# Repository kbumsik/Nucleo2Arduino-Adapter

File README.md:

Universal Shields Adapter for STM32 Nucleo 64 boards
====================================================

Universal Adapter for Nucleo 64 boards that supports various expansion boards
including:

* STM32 Nucleo pinsas a mother
* Arduino shields, **including ICSP(SPI) pins**
* TI BoosterPack (LaunchPad) 40-pin
* 2 x Atmel Xplained Pro expansion boards

Image (v0.5 test board)
=======================

Why?
====

STM32 Nucleo boards are awesome development boards to start a microcontroller
project. However, ther is a caveat: it does not have variaous expansion boards.
Even though Nucleo boards have Arduino-compatible header pins, a problem still
aries here:

> *Nucleo boards do not have Arduino ICSP/SPI pins!*

Absence of ICSP pins losses supports for various arduino shields. So I decided
to make an adapter shield to support for Arduino shields. Making this adapter I
also added some headers for other companies expansion boards like TI's BoosterPack.

I believe this adapter will remove nasty wiring jobs when you work with expansion boards.

Tested expansion boards
=======================
Although this adapter will support most of Arduino shields and expansion boards
we are always unexpected things making it not to supports some boards. So I attach
tested expansion boards here

* ATWINC1500 Xplained Pro

Please email me (kbumsik@gmail.com) or PR if you tested other boards.

External Libraries Used
=======================
I used the following libraries:

* [KiCad Library](https://github.com/KiCad/kicad-library/tree/master/template)

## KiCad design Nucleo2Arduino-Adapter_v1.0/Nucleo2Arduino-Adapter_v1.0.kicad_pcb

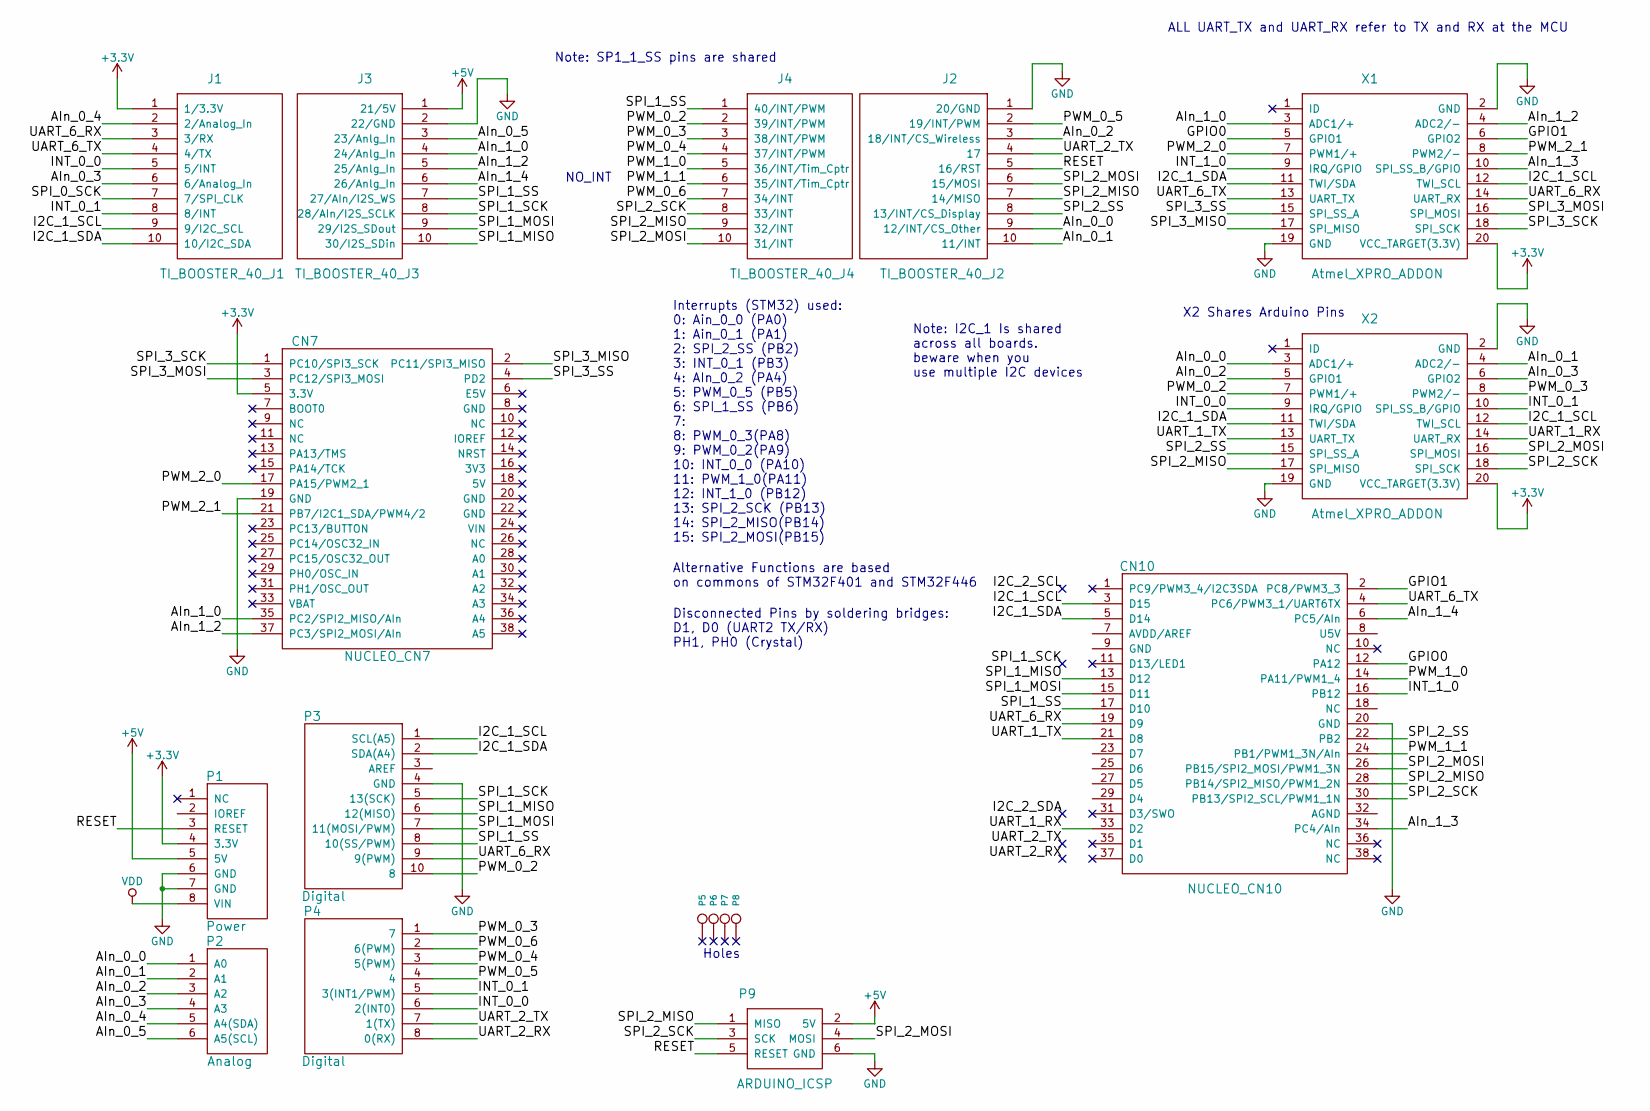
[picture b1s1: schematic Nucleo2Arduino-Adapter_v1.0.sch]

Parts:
CN7: NUCLEO_CN7; Pin_Header_Straight_2x19
CN10: NUCLEO_CN10; Pin_Header_Straight_2x19
J1: TI_BOOSTER_40_J1; SIL-10
J2: TI_BOOSTER_40_J2; SIL-10
J3: TI_BOOSTER_40_J3; SIL-10
J4: TI_BOOSTER_40_J4; SIL-10
P1: Power; Socket_Strip_Arduino_1x08
P2: Analog; Socket_Strip_Arduino_1x06
P3: Digital; Socket_Strip_Arduino_1x10
P4: Digital; Socket_Strip_Arduino_1x08
P5, P6, P7, P8: CONN_1; Arduino_1pin
P9: ARDUINO_ICSP; Pin_Header_Straight_2x03
X1, X2: Atmel_XPRO_ADDON; Pin_Header_Angled_2x10

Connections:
+3V3: CN7.5 (3.3V), J1.1 (1/3.3V), P1.4 (3.3V), X1.20 (VCC_TARGET(3.3V)), X2.20 (VCC_TARGET(3.3V))
+5V: J3.1 (21/5V), P1.5 (5V), P9.2 (5V)
/AIn_0_0: J2.9 (12/INT/CS_Other), P2.1 (A0), X2.3 (ADC1/+)
/AIn_0_1: J2.10 (11/INT), P2.2 (A1), X2.4 (ADC2/-)
/AIn_0_2: J2.3 (18/INT/CS_Wireless), P2.3 (A2), X2.5 (GPIO1)
/AIn_0_3: J1.6 (6/Analog_In), P2.4 (A3), X2.6 (GPIO2)
/AIn_0_4: J1.2 (2/Analog_In), P2.5 (A4(SDA))
/AIn_0_5: J3.3 (23/Anlg_In), P2.6 (A5(SCL))
/AIn_1_0: CN7.35 (PC2/SPI2_MISO/AIn), J3.4 (24/Anlg_In), X1.3 (ADC1/+)
/AIn_1_2: CN7.37 (PC3/SPI2_MOSI/AIn), J3.5 (25/Anlg_In), X1.4 (ADC2/-)
/AIn_1_3: CN10.34 (PC4/AIn), X1.10 (SPI_SS_B/GPIO)
/AIn_1_4: CN10.6 (PC5/AIn), J3.6 (26/Anlg_In)
/GPIO0: CN10.12 (PA12), X1.5 (GPIO1)
/GPIO1: CN10.2 (PC8/PWM3_3), X1.6 (GPIO2)
/I2C_1_SCL: CN10.3 (D15), J1.9 (9/I2C_SCL), P3.1 (SCL(A5)), X1.12 (TWI_SCL), X2.12 (TWI_SCL)
/I2C_1_SDA: CN10.5 (D14), J1.10 (10/I2C_SDA), P3.2 (SDA(A4)), X1.11 (TWI/SDA), X2.11 (TWI/SDA)
/INT_0_0: J1.5 (5/INT), P4.6 (2(INT0)), X2.9 (IRQ/GPIO)
/INT_0_1: J1.8 (8/INT), P4.5 (3(INT1/PWM)), X2.10 (SPI_SS_B/GPIO)
/INT_1_0: CN10.16 (PB12), X1.9 (IRQ/GPIO)
/PWM_0_2: J4.2 (39/INT/PWM), P3.10 (8), X2.7 (PWM1/+)
/PWM_0_3: J4.3 (38/INT/PWM), P4.1 (7), X2.8 (PWM2/-)
/PWM_0_4: J4.4 (37/INT/PWM), P4.3 (5(PWM))
/PWM_0_5: J2.2 (19/INT/PWM), P4.4
/PWM_0_6: J4.7 (34/INT), P4.2 (6(PWM))
/PWM_1_0: CN10.14 (PA11/PWM1_4), J4.5 (36/INT/Tim_Cptr)
/PWM_1_1: CN10.24 (PB1/PWM1_3N/AIn), J4.6 (35/INT/Tim_Cptr)
/PWM_2_0: CN7.17 (PA15/PWM2_1), X1.7 (PWM1/+)
/PWM_2_1: CN7.21 (PB7/I2C1_SDA/PWM4/2), X1.8 (PWM2/-)
/RESET: J2.5 (16/RST), P1.3 (RESET), P9.5 (RESET)
/SPI_0_SCK: J1.7 (7/SPI_CLK)
/SPI_1_MISO: CN10.13 (D12), J3.10 (30/I2S_SDin), P3.6 (12(MISO))
/SPI_1_MOSI: CN10.15 (D11), J3.9 (29/I2S_SDout), P3.7 (11(MOSI/PWM))
/SPI_1_SCK: J3.8 (28/AIn/I2S_SCLK), P3.5 (13(SCK))
/SPI_1_SS: CN10.17 (D10), J3.7 (27/AIn/I2S_WS), J4.1 (40/INT/PWM), P3.8 (10(SS/PWM))
/SPI_2_MISO: CN10.28 (PB14/SPI2_MISO/PWM1_2N), J2.7 (14/MISO), J4.9 (32/INT), P9.1 (MISO), X2.17 (SPI_MISO)
/SPI_2_MOSI: CN10.26 (PB15/SPI2_MOSI/PWM1_3N), J2.6 (15/MOSI), J4.10 (31/INT), P9.4 (MOSI), X2.16 (SPI_MOSI)
/SPI_2_SCK: CN10.30 (PB13/SPI2_SCL/PWM1_1N), J4.8 (33/INT), P9.3 (SCK), X2.18 (SPI_SCK)
/SPI_2_SS: CN10.22 (PB2), J2.8 (13/INT/CS_Display), X2.15 (SPI_SS_A)
/SPI_3_MISO: CN7.2 (PC11/SPI3_MISO), X1.17 (SPI_MISO)
/SPI_3_MOSI: CN7.3 (PC12/SPI3_MOSI), X1.16 (SPI_MOSI)
/SPI_3_SCK: CN7.1 (PC10/SPI3_SCK), X1.18 (SPI_SCK)
/SPI_3_SS: CN7.4 (PD2), X1.15 (SPI_SS_A)
/UART_1_RX: CN10.33 (D2), X2.14 (UART_RX)
/UART_1_TX: CN10.21 (D8), X2.13 (UART_TX)
/UART_2_RX: P4.8 (0(RX))
/UART_2_TX: J2.4 (17), P4.7 (1(TX))
/UART_6_RX: CN10.19 (D9), J1.3 (3/RX), P3.9 (9(PWM)), X1.14 (UART_RX)
/UART_6_TX: CN10.4 (PC6/PWM3_1/UART6TX), J1.4 (4/TX), X1.13 (UART_TX)
GND: CN7.19 (GND), CN10.20 (GND), J2.1 (20/GND), J3.2 (22/GND), P1.6 (GND), P1.7 (GND), P3.4 (GND), P9.6 (GND), X1.2 (GND), X1.19 (GND), X2.2 (GND), X2.19 (GND)
VDD: P1.8 (VIN)

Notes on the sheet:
Holes
Alternative Functions are based on commons of STM32F401 and STM32F446
ALL UART_TX and UART_RX refer to TX and RX at the MCU
X2 Shares Arduino Pins
Disconnected Pins by soldering bridges: D1, D0 (UART2 TX/RX) PH1, PH0 (Crystal)
Interrupts (STM32) used: 0: Ain_0_0 (PA0) 1: Ain_0_1 (PA1) 2: SPI_2_SS (PB2) 3: INT_0_1 (PB3) 4: AIn_0_2 (PA4) 5: PWM_0_5 (PB5) 6: SPI_1_SS (PB6) 7: 8: PWM_0_3(PA8) 9: PWM_0_2(PA9) 10: INT_0_0 (PA10) 11: PWM_1_0(PA11) 12: INT_1_0 (PB12) 13: SPI_2_SCK (PB13) 14: SPI_2_MISO(PB14) 15: SPI_2_MOSI(PB15)
NO_INT
Note: SP1_1_SS pins are shared
Note: I2C_1 Is shared across all boards. beware when you use multiple I2C devices

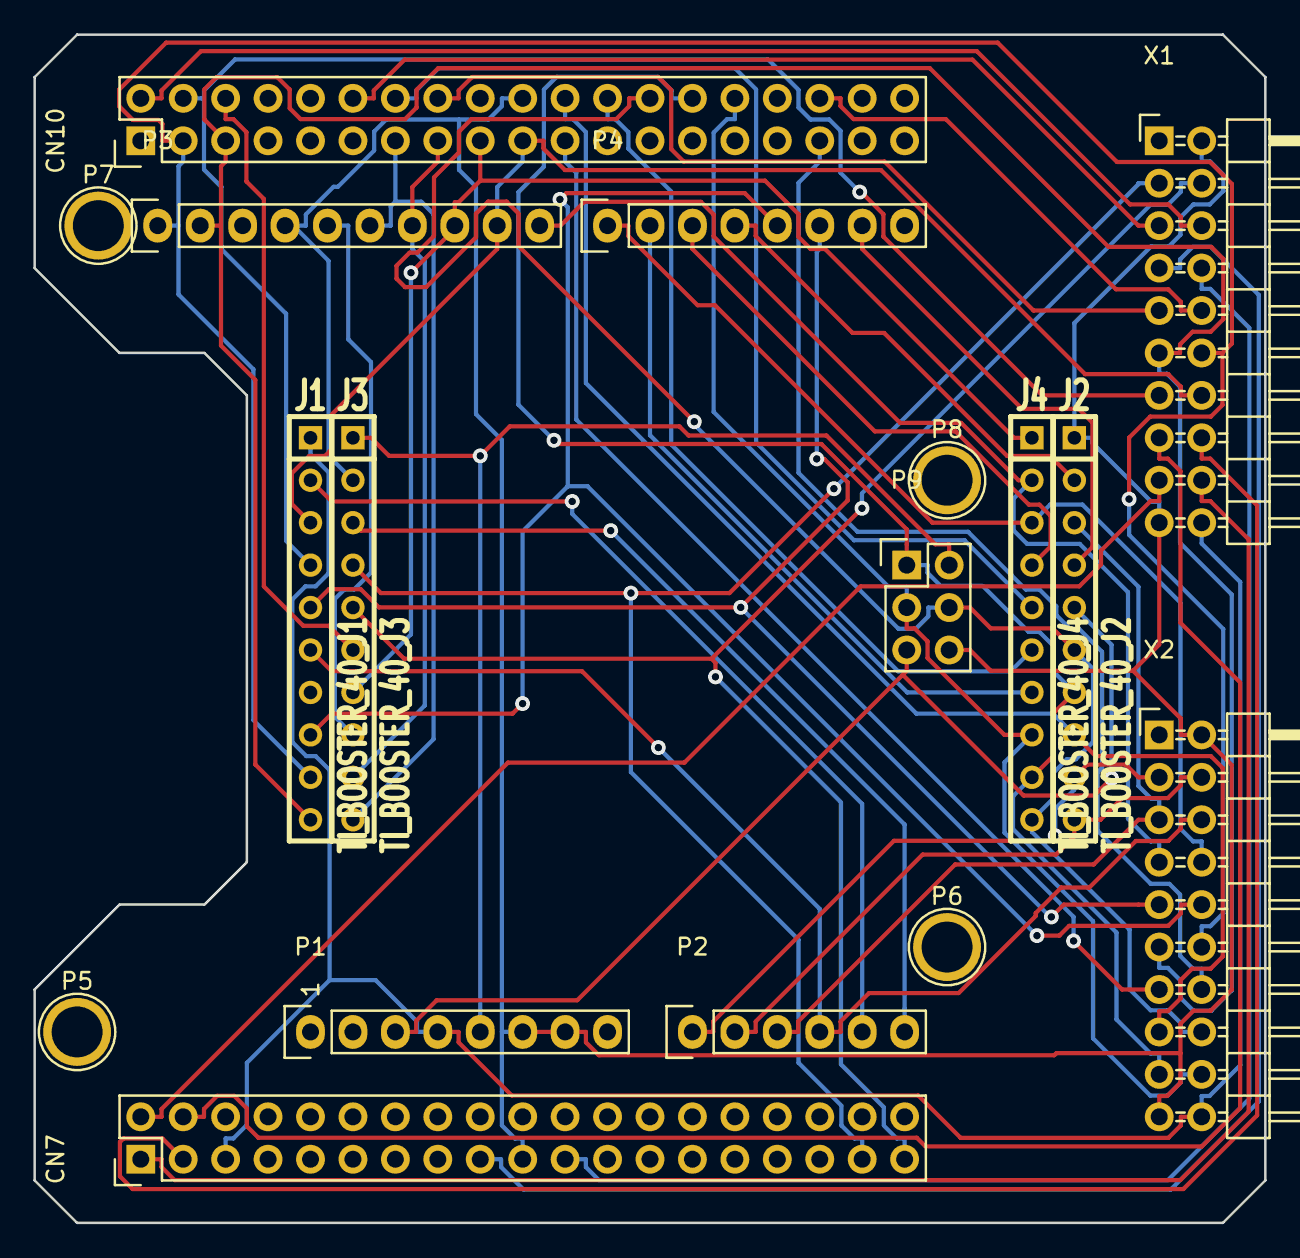
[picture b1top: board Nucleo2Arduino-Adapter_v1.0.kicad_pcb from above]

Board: 2 copper layers, 73.7 x 71.1 mm, 17 parts (0 on the bottom side), 47 nets.

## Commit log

2016-11-26 added Arduino and TI boosterpack
2016-11-29 fixed Arduino pin symbol
2016-11-29 Added ICSP header, Fixed Ardino/BSTPCK Symbols, Added connection
2016-11-30 added Nucleo Zio and Atmel XPro Header symbol
2016-12-06 First draft of connection. Completed PCB pin position
2016-12-07 Connections and PCB footprint completed. Needs routing
2016-12-08 Generated gerber files. Placed a first order
2016-12-08 Updated README and pdf files
2016-12-08 Fixed images in README.MD
